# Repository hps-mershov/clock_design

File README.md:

# clock_design
 My first clock design.

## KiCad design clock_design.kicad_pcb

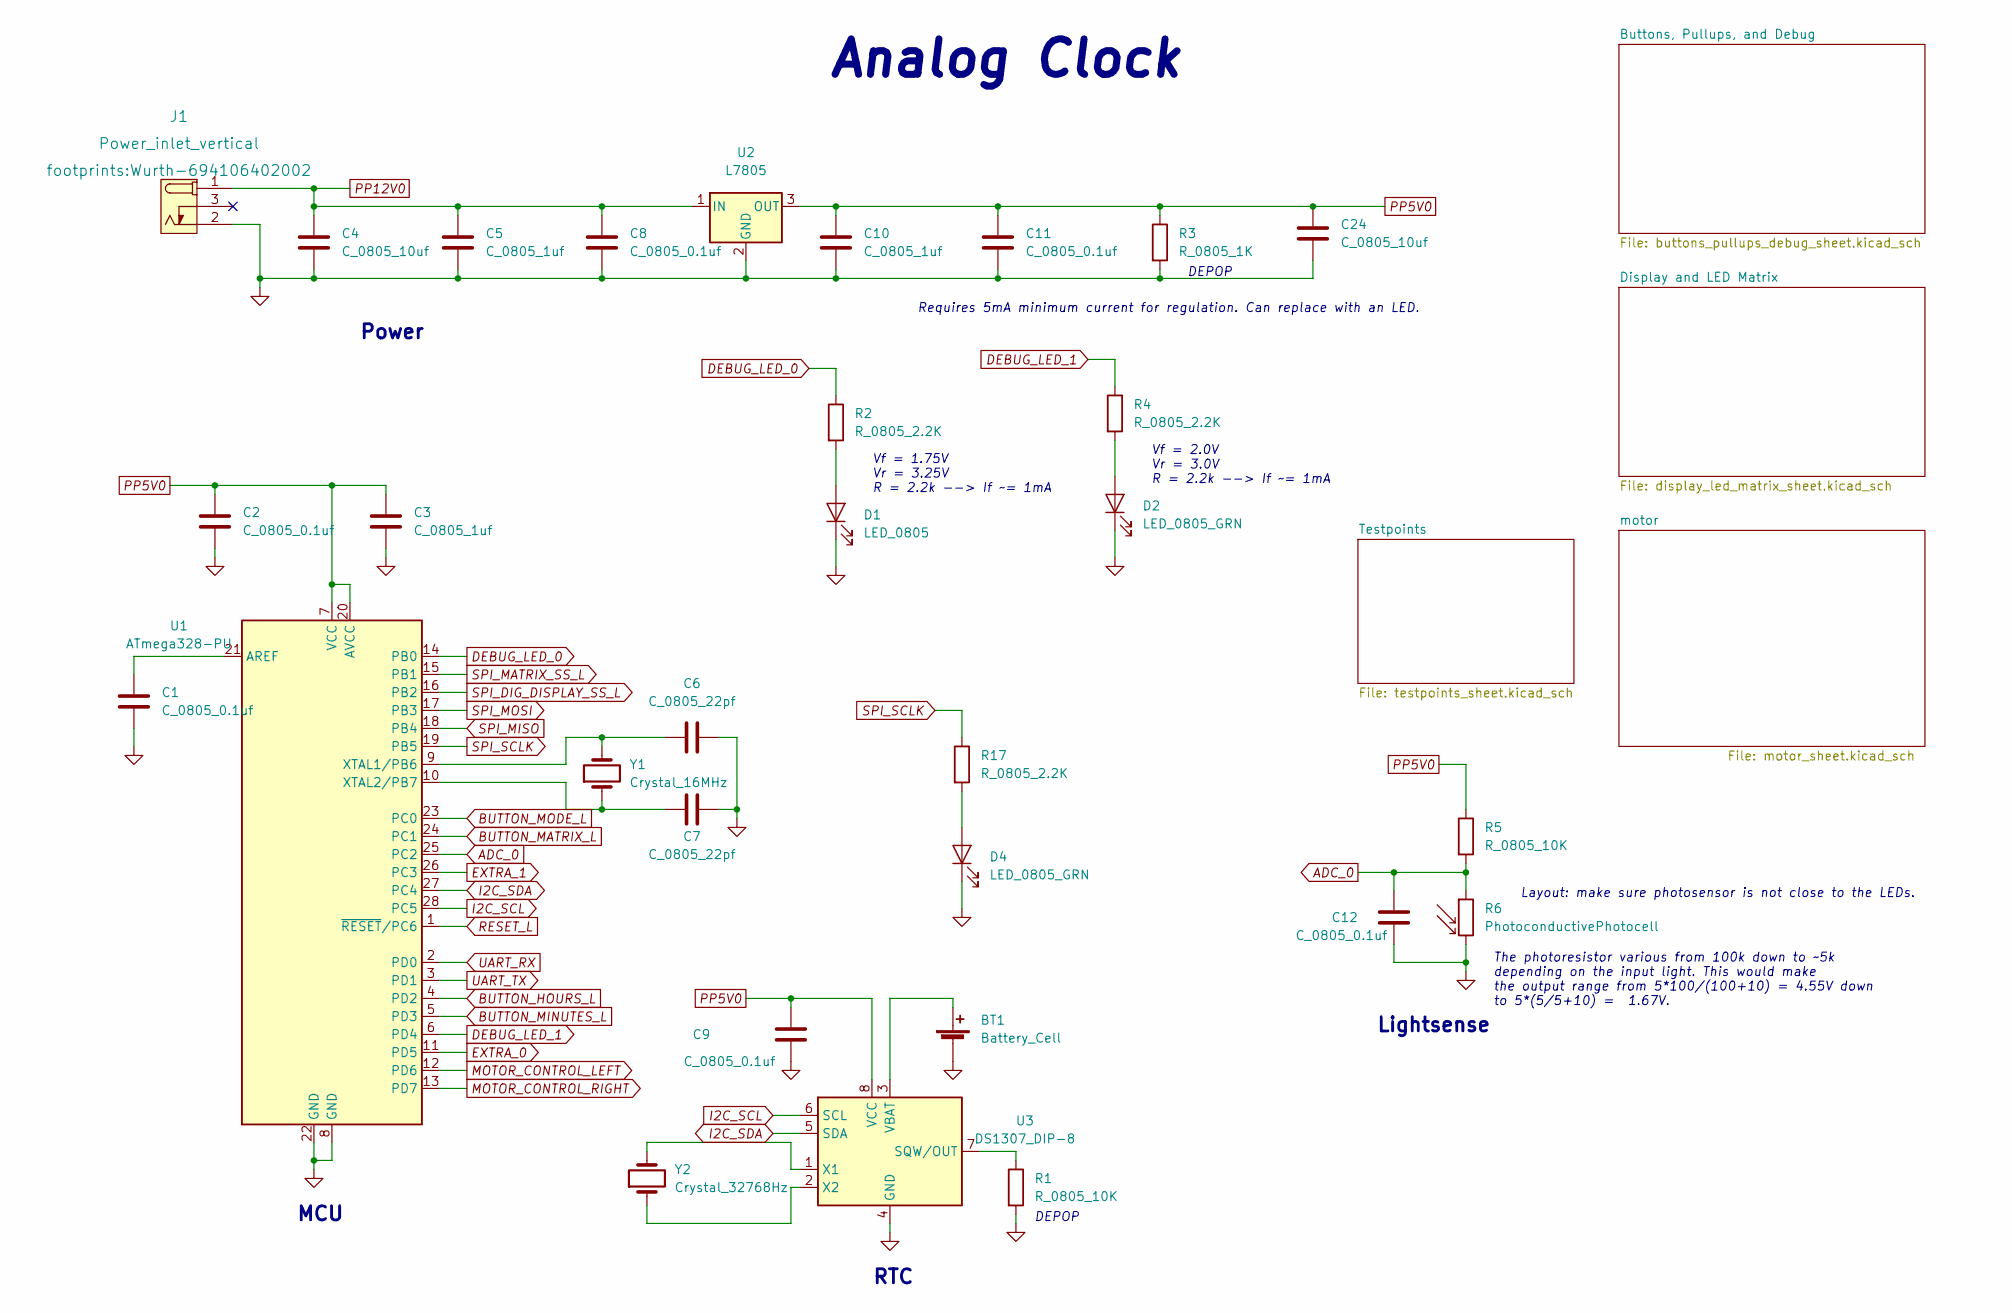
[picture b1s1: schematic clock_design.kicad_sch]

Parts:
BT1: Battery_Cell; BatteryHolder_Keystone_106_1x20mm; MPN BS-7; Digikey PN BS-7-ND
C1, C2, C8, C9, C11, C12: C_0805_0.1uf; C_0805_2012Metric; Voltage N/A; Tolerance N/A; MPN 08055C104KAT2A; Digikey PN 478-1395-1-ND
C3, C5, C10: C_0805_1uf; C_0805_2012Metric; Voltage N/A; Tolerance N/A; MPN CC0805KKX7R8BB105; Digikey PN 311-1456-1-ND
C4, C24: C_0805_10uf; C_0805_2012Metric; Voltage N/A; Tolerance N/A; MPN GRM21BR61E106KA73L; Digikey PN 490-5523-1-ND
C6, C7: C_0805_22pf; C_0805_2012Metric; Voltage N/A; Tolerance N/A; MPN CC0805JRNPO9BN220; Digikey PN 311-1103-1-ND
D1: LED_0805; LED_0805_2012Metric; MPN 150080RS75000; Digikey PN 732-4984-1-ND
D2, D4: LED_0805_GRN; LED_0805_2012Metric; MPN 150080VS75000; Digikey PN 732-4986-1-ND
J1: Power_inlet_vertical; Wurth-694106402002; MPN 694106402002; Digikey PN 732-5931-ND
R1, R5: R_0805_10K; R_0805_2012Metric; Tolerance N/A; MPN RC0805FR-0710KL; Digikey PN 311-10.0KCRCT-ND
R2, R4, R17: R_0805_2.2K; R_0805_2012Metric; Tolerance N/A; MPN N/A; Digikey PN 311-2.20KCRCT-ND
R3: R_0805_1K; R_0805_2012Metric; Tolerance N/A; Mouser PN N/A; Digikey PN RC0805FR-0710KL
R6: PhotoconductivePhotocell; R_LDR_4.9x4.2mm_P2.54mm_Vertical; Voltage N/A; Tolerance N/A; MPN PDV-P8103; Digikey PN PDV-P8103-ND
U1: ATmega328-PU; DIP-28_W7.62mm; MPN ED281DT; Digikey PN ED3050-5-ND
U2: L7805; TO-252-2
U3: DS1307_DIP-8; DIP-8_W7.62mm; MPN A 08-LC-TT; Digikey PN AE9986-ND
Y1: Crystal_16MHz; Crystal_SMD_HC49-SD; MPN ECS-160-20-5PXDN-TR; Digikey PN XC1299CT-ND
Y2: Crystal_32768Hz; Crystal_SMD_2Pin_3.2x1.5mm; MPN Q 0,032768-JTX310-12,5-20-T1-HMR-50K-LF; Digikey PN 1908-1314-1-ND

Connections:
ADC_0: C12.1, R5.2, R6.1, U1.25 (PC2)
BUTTON_HOURS_L: U1.4 (PD2); also elsewhere on the board
BUTTON_MATRIX_L: U1.24 (PC1); also elsewhere on the board
BUTTON_MINUTES_L: U1.5 (PD3); also elsewhere on the board
BUTTON_MODE_L: U1.23 (PC0); also elsewhere on the board
DEBUG_LED_0: R2.1, U1.14 (PB0); also elsewhere on the board
DEBUG_LED_1: R4.1, U1.6 (PD4)
EXTRA_0: U1.11 (PD5); also elsewhere on the board
EXTRA_1: U1.26 (PC3); also elsewhere on the board
GND: BT1.2 (-), C1.2, C2.2, C3.2, C4.2, C5.2, C6.2, C7.2, C8.2, C9.2, C10.2, C11.2, C12.2, C24.2, D1.1 (K), D2.1 (K), D4.1 (K), J1.2 (OUT), R1.2, R3.2, R6.2, U1.8 (GND), U1.22 (GND), U2.2 (GND), U3.4 (GND); also elsewhere on the board
I2C_SCL: U1.28 (PC5), U3.6 (SCL); also elsewhere on the board
I2C_SDA: U1.27 (PC4), U3.5 (SDA); also elsewhere on the board
MOTOR_CONTROL_LEFT: U1.12 (PD6); also elsewhere on the board
MOTOR_CONTROL_RIGHT: U1.13 (PD7); also elsewhere on the board
unnamed: BT1.1 (+), U3.3 (VBAT)
unnamed: C1.1, U1.21 (AREF)
unnamed: C6.1, U1.9 (XTAL1/PB6), Y1.2
unnamed: C7.1, U1.10 (XTAL2/PB7), Y1.1
unnamed: D1.2 (A), R2.2
unnamed: D2.2 (A), R4.2
unnamed: D4.2 (A), R17.2
unnamed: R1.1, U3.7 (SQW/OUT)
unnamed: U3.1 (X1), Y2.2
unnamed: U3.2 (X2), Y2.1
PP5V0: C2.1, C3.1, C9.1, C10.1, C11.1, C24.1, R3.1, R5.1, U1.7 (VCC), U1.20 (AVCC), U2.3 (OUT), U3.8 (VCC); also elsewhere on the board
PP12V0: C4.1, C5.1, C8.1, J1.1 (POLE), U2.1 (IN); also elsewhere on the board
RESET_L: U1.1 (~RESET/PC6); also elsewhere on the board
SPI_DIG_DISPLAY_SS_L: U1.16 (PB2); also elsewhere on the board
SPI_MATRIX_SS_L: U1.15 (PB1); also elsewhere on the board
SPI_MISO: U1.18 (PB4); also elsewhere on the board
SPI_MOSI: U1.17 (PB3); also elsewhere on the board
SPI_SCLK: R17.1, U1.19 (PB5); also elsewhere on the board
UART_RX: U1.2 (PD0); also elsewhere on the board
UART_TX: U1.3 (PD1); also elsewhere on the board

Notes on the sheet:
Vf = 1.75V Vr = 3.25V R = 2.2k --> If ~= 1mA
RTC
MCU
DEPOP
The photoresistor various from 100k down to ~5k depending on the input light. This would make the output range from 5*100/(100+10) = 4.55V down to 5*(5/5+10) = 1.67V.
Analog Clock
Power
Vf = 2.0V Vr = 3.0V R = 2.2k --> If ~= 1mA
Layout: make sure photosensor is not close to the LEDs.
Requires 5mA minimum current for regulation. Can replace with an LED.
Lightsense

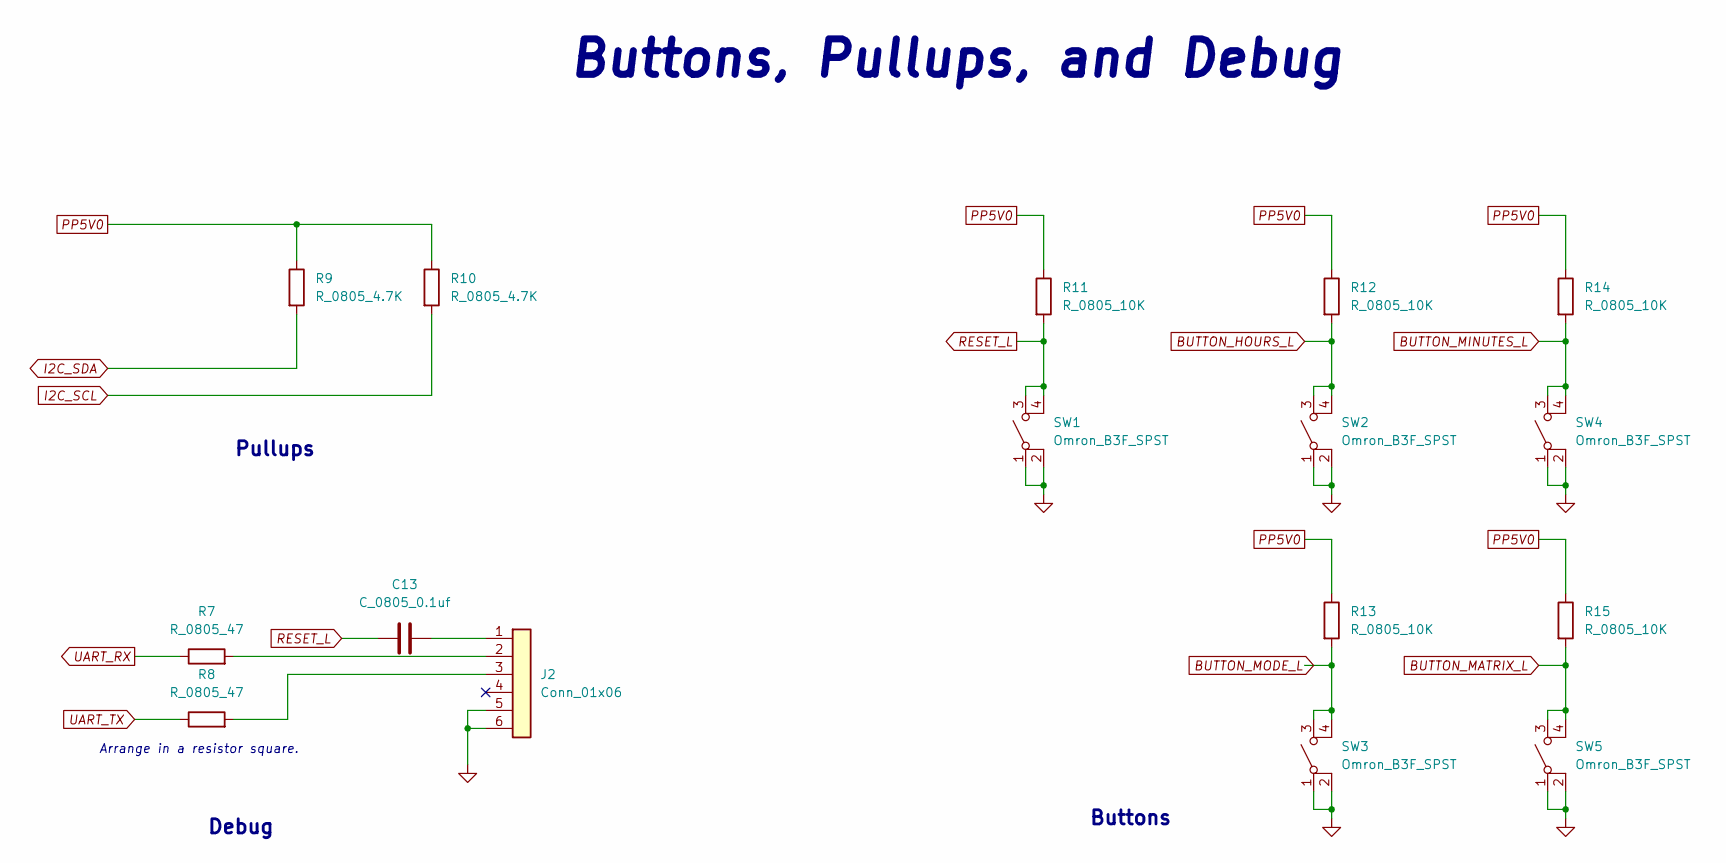
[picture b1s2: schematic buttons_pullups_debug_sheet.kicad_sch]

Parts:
C13: C_0805_0.1uf; C_0805_2012Metric; Voltage N/A; Tolerance N/A; MPN 08055C104KAT2A; Digikey PN 478-1395-1-ND
J2: Conn_01x06; PinHeader_1x06_P2.54mm_Vertical; MPN 61300611121; Digikey PN 732-5319-ND
R7, R8: R_0805_47; R_0805_2012Metric; Tolerance N/A; Mouser PN N/A; Digikey PN RC0805FR-0747RL
R9, R10: R_0805_4.7K; R_0805_2012Metric; Tolerance N/A; MPN RC0805FR-074K7L; Digikey PN 311-4.70KCRCT-ND
R11, R12, R13, R14, R15: R_0805_10K; R_0805_2012Metric; Tolerance N/A; MPN RC0805FR-0710KL; Digikey PN 311-10.0KCRCT-ND
SW1, SW2, SW3, SW4, SW5: Omron_B3F_SPST; SW_SPST_Omron_B3FS-100xP; MPN B3FS-1000P; Digikey PN SW423CT-ND

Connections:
BUTTON_HOURS_L: R12.2, SW2.3 (B), SW2.4 (B); also elsewhere on the board
BUTTON_MATRIX_L: R15.2, SW5.3 (B), SW5.4 (B); also elsewhere on the board
BUTTON_MINUTES_L: R14.2, SW4.3 (B), SW4.4 (B); also elsewhere on the board
BUTTON_MODE_L: R13.2, SW3.3 (B), SW3.4 (B); also elsewhere on the board
GND: J2.5, J2.6, SW1.1 (A), SW1.2 (A), SW2.1 (A), SW2.2 (A), SW3.1 (A), SW3.2 (A), SW4.1 (A), SW4.2 (A), SW5.1 (A), SW5.2 (A); also elsewhere on the board
I2C_SCL: R10.2; also elsewhere on the board
I2C_SDA: R9.2; also elsewhere on the board
unnamed: C13.2, J2.1
unnamed: J2.2, R7.2
unnamed: J2.3, R8.2
PP5V0: R9.1, R10.1, R11.1, R12.1, R13.1, R14.1, R15.1; also elsewhere on the board
RESET_L: C13.1, R11.2, SW1.3 (B), SW1.4 (B); also elsewhere on the board
UART_RX: R7.1; also elsewhere on the board
UART_TX: R8.1; also elsewhere on the board

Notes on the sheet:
Debug
Buttons, Pullups, and Debug
Pullups
Buttons
Arrange in a resistor square.

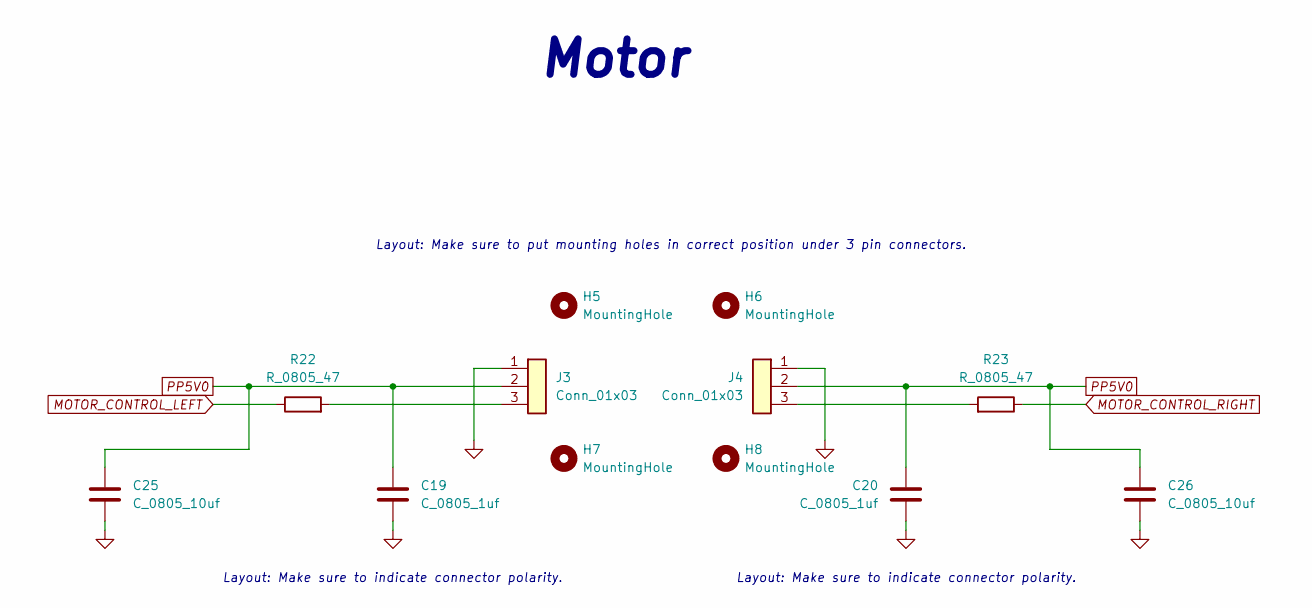
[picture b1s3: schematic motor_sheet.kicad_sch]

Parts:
C19, C20: C_0805_1uf; C_0805_2012Metric; Voltage N/A; Tolerance N/A; MPN CC0805KKX7R8BB105; Digikey PN 311-1456-1-ND
C25, C26: C_0805_10uf; C_0805_2012Metric; Voltage N/A; Tolerance N/A; MPN GRM21BR61E106KA73L; Digikey PN 490-5523-1-ND
H5, H6, H7, H8: MountingHole; MountingHole_3.2mm_M3
J3, J4: Conn_01x03; PinHeader_1x03_P2.54mm_Vertical; MPN 61300311121; Digikey PN 732-5316-ND
R22, R23: R_0805_47; R_0805_2012Metric; Tolerance N/A; Mouser PN N/A; Digikey PN RC0805FR-0747RL

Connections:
GND: C19.2, C20.2, C25.2, C26.2, J3.1, J4.1; also elsewhere on the board
MOTOR_CONTROL_LEFT: R22.1; also elsewhere on the board
MOTOR_CONTROL_RIGHT: R23.1; also elsewhere on the board
unnamed: J3.3, R22.2
unnamed: J4.3, R23.2
PP5V0: C19.1, C20.1, C25.1, C26.1, J3.2, J4.2; also elsewhere on the board

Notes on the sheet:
Motor
Layout: Make sure to indicate connector polarity.
Layout: Make sure to put mounting holes in correct position under 3 pin connectors.

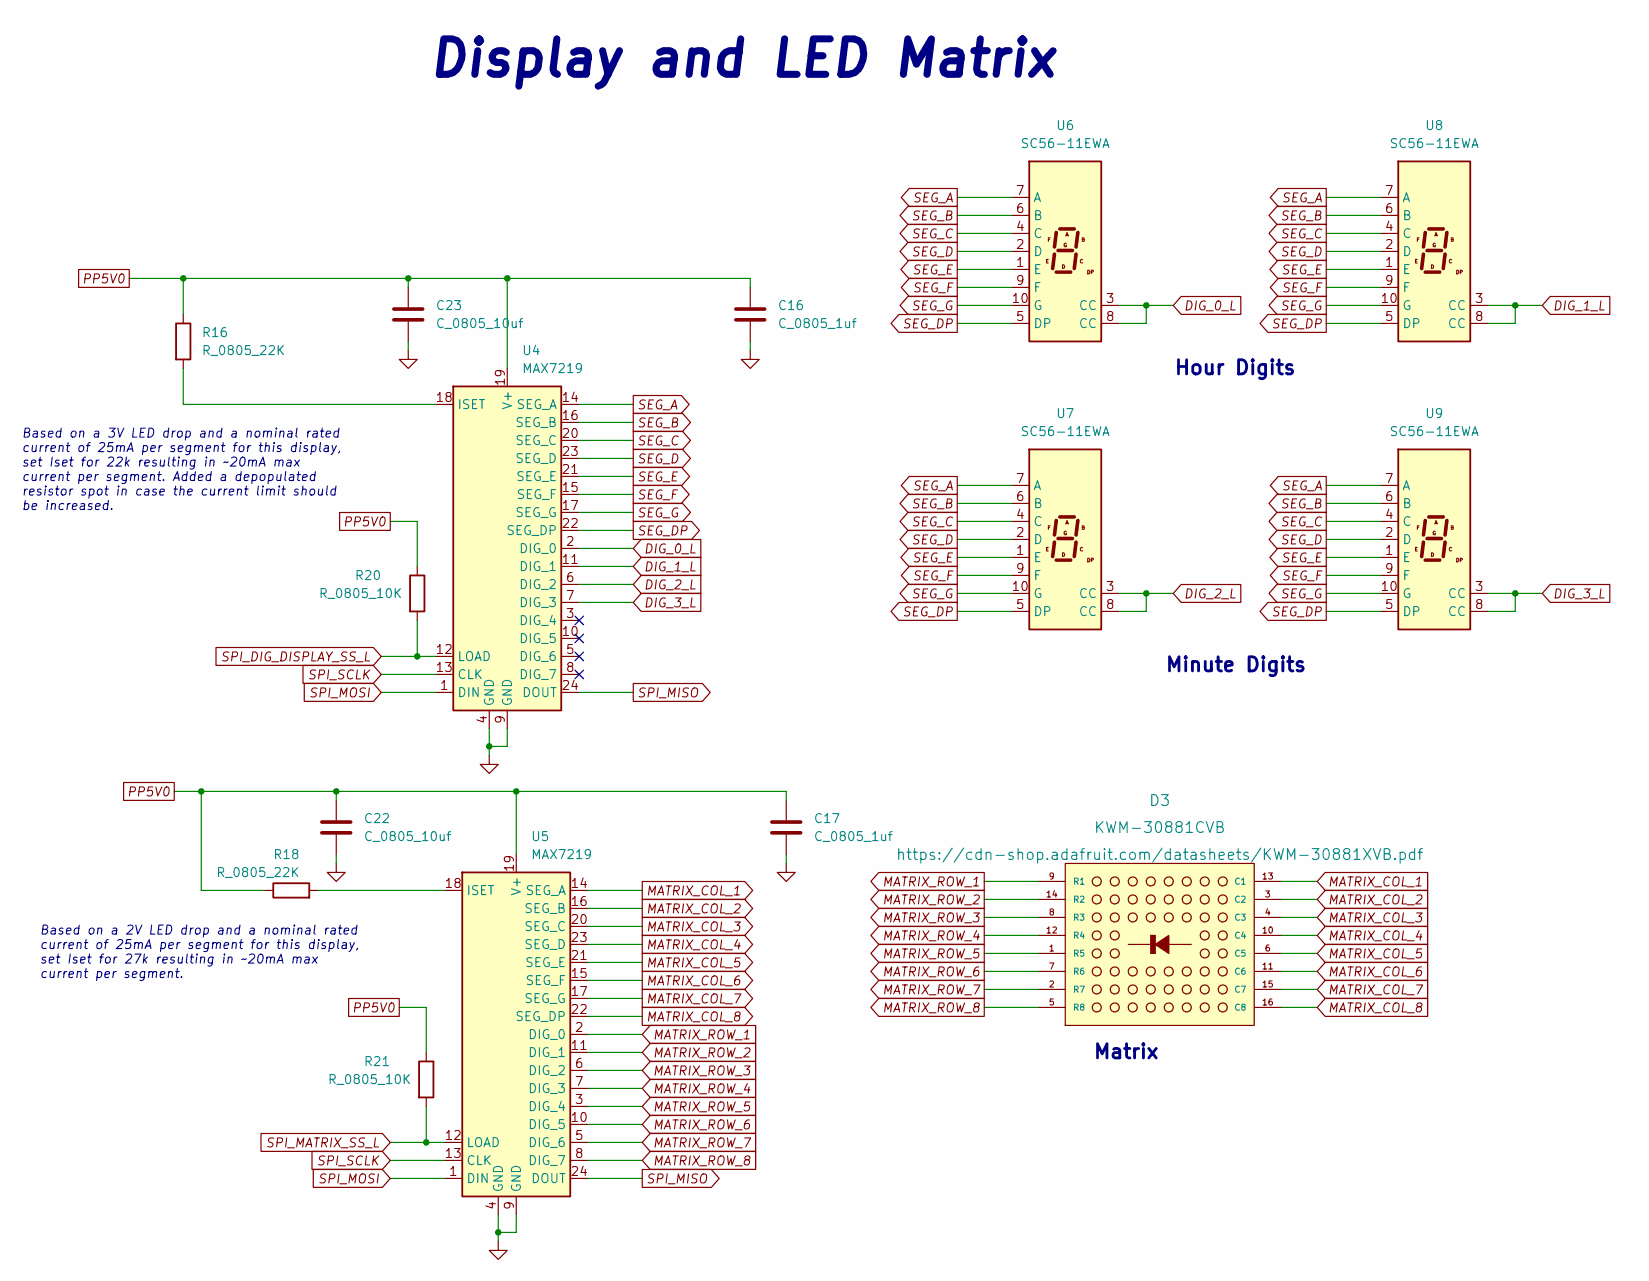
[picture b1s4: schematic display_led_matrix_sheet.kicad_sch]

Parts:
C16, C17: C_0805_1uf; C_0805_2012Metric; Voltage N/A; Tolerance N/A; MPN CC0805KKX7R8BB105; Digikey PN 311-1456-1-ND
C22, C23: C_0805_10uf; C_0805_2012Metric; Voltage N/A; Tolerance N/A; MPN GRM21BR61E106KA73L; Digikey PN 490-5523-1-ND
D3: KWM-30881CVB; MPN KWM-30881CVB; Digikey PN N/A
R16, R18: R_0805_22K; R_0805_2012Metric; Tolerance N/A; MPN RC0805FR-0722KL; Digikey PN 311-22.0KCRCT-ND
R20, R21: R_0805_10K; R_0805_2012Metric; Tolerance N/A; MPN RC0805FR-0710KL; Digikey PN 311-10.0KCRCT-ND
U4, U5: MAX7219; DIP-24_W7.62mm; MPN ED241DT; Digikey PN ED3049-5-ND
U6, U7, U8, U9: SC56-11EWA; Sx56-1xxxxx; Digikey PN 754-1465-5-ND

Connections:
DIG_0_L: U4.2 (DIG_0), U6.3 (CC), U6.8 (CC)
DIG_1_L: U4.11 (DIG_1), U8.3 (CC), U8.8 (CC)
DIG_2_L: U4.6 (DIG_2), U7.3 (CC), U7.8 (CC)
DIG_3_L: U4.7 (DIG_3), U9.3 (CC), U9.8 (CC)
GND: C16.2, C17.2, C22.2, C23.2, U4.4 (GND), U4.9 (GND), U5.4 (GND), U5.9 (GND); also elsewhere on the board
MATRIX_COL_1: D3.13 (C1), U5.14 (SEG_A)
MATRIX_COL_2: D3.3 (C2), U5.16 (SEG_B)
MATRIX_COL_3: D3.4 (C3), U5.20 (SEG_C)
MATRIX_COL_4: D3.10 (C4), U5.23 (SEG_D)
MATRIX_COL_5: D3.6 (C5), U5.21 (SEG_E)
MATRIX_COL_6: D3.11 (C6), U5.15 (SEG_F)
MATRIX_COL_7: D3.15 (C7), U5.17 (SEG_G)
MATRIX_COL_8: D3.16 (C8), U5.22 (SEG_DP)
MATRIX_ROW_1: D3.9 (R1), U5.2 (DIG_0)
MATRIX_ROW_2: D3.14 (R2), U5.11 (DIG_1)
MATRIX_ROW_3: D3.8 (R3), U5.6 (DIG_2)
MATRIX_ROW_4: D3.12 (R4), U5.7 (DIG_3)
MATRIX_ROW_5: D3.1 (R5), U5.3 (DIG_4)
MATRIX_ROW_6: D3.7 (R6), U5.10 (DIG_5)
MATRIX_ROW_7: D3.2 (R7), U5.5 (DIG_6)
MATRIX_ROW_8: D3.5 (R8), U5.8 (DIG_7)
unnamed: R16.2, U4.18 (ISET)
unnamed: R18.2, U5.18 (ISET)
PP5V0: C16.1, C17.1, C22.1, C23.1, R16.1, R18.1, R20.1, R21.1, U4.19 (V+), U5.19 (V+); also elsewhere on the board
SEG_A: U4.14 (SEG_A), U6.7 (A), U7.7 (A), U8.7 (A), U9.7 (A)
SEG_B: U4.16 (SEG_B), U6.6 (B), U7.6 (B), U8.6 (B), U9.6 (B)
SEG_C: U4.20 (SEG_C), U6.4 (C), U7.4 (C), U8.4 (C), U9.4 (C)
SEG_D: U4.23 (SEG_D), U6.2 (D), U7.2 (D), U8.2 (D), U9.2 (D)
SEG_DP: U4.22 (SEG_DP), U6.5 (DP), U7.5 (DP), U8.5 (DP), U9.5 (DP)
SEG_E: U4.21 (SEG_E), U6.1 (E), U7.1 (E), U8.1 (E), U9.1 (E)
SEG_F: U4.15 (SEG_F), U6.9 (F), U7.9 (F), U8.9 (F), U9.9 (F)
SEG_G: U4.17 (SEG_G), U6.10 (G), U7.10 (G), U8.10 (G), U9.10 (G)
SPI_DIG_DISPLAY_SS_L: R20.2, U4.12 (LOAD); also elsewhere on the board
SPI_MATRIX_SS_L: R21.2, U5.12 (LOAD); also elsewhere on the board
SPI_MISO: U4.24 (DOUT), U5.24 (DOUT); also elsewhere on the board
SPI_MOSI: U4.1 (DIN), U5.1 (DIN); also elsewhere on the board
SPI_SCLK: U4.13 (CLK), U5.13 (CLK); also elsewhere on the board

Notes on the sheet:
Hour Digits
Minute Digits
Based on a 3V LED drop and a nominal rated current of 25mA per segment for this display, set Iset for 22k resulting in ~20mA max current per segment. Added a depopulated resistor spot in case the current limit should be increased.
Matrix
Display and LED Matrix
Based on a 2V LED drop and a nominal rated current of 25mA per segment for this display, set Iset for 27k resulting in ~20mA max current per segment.

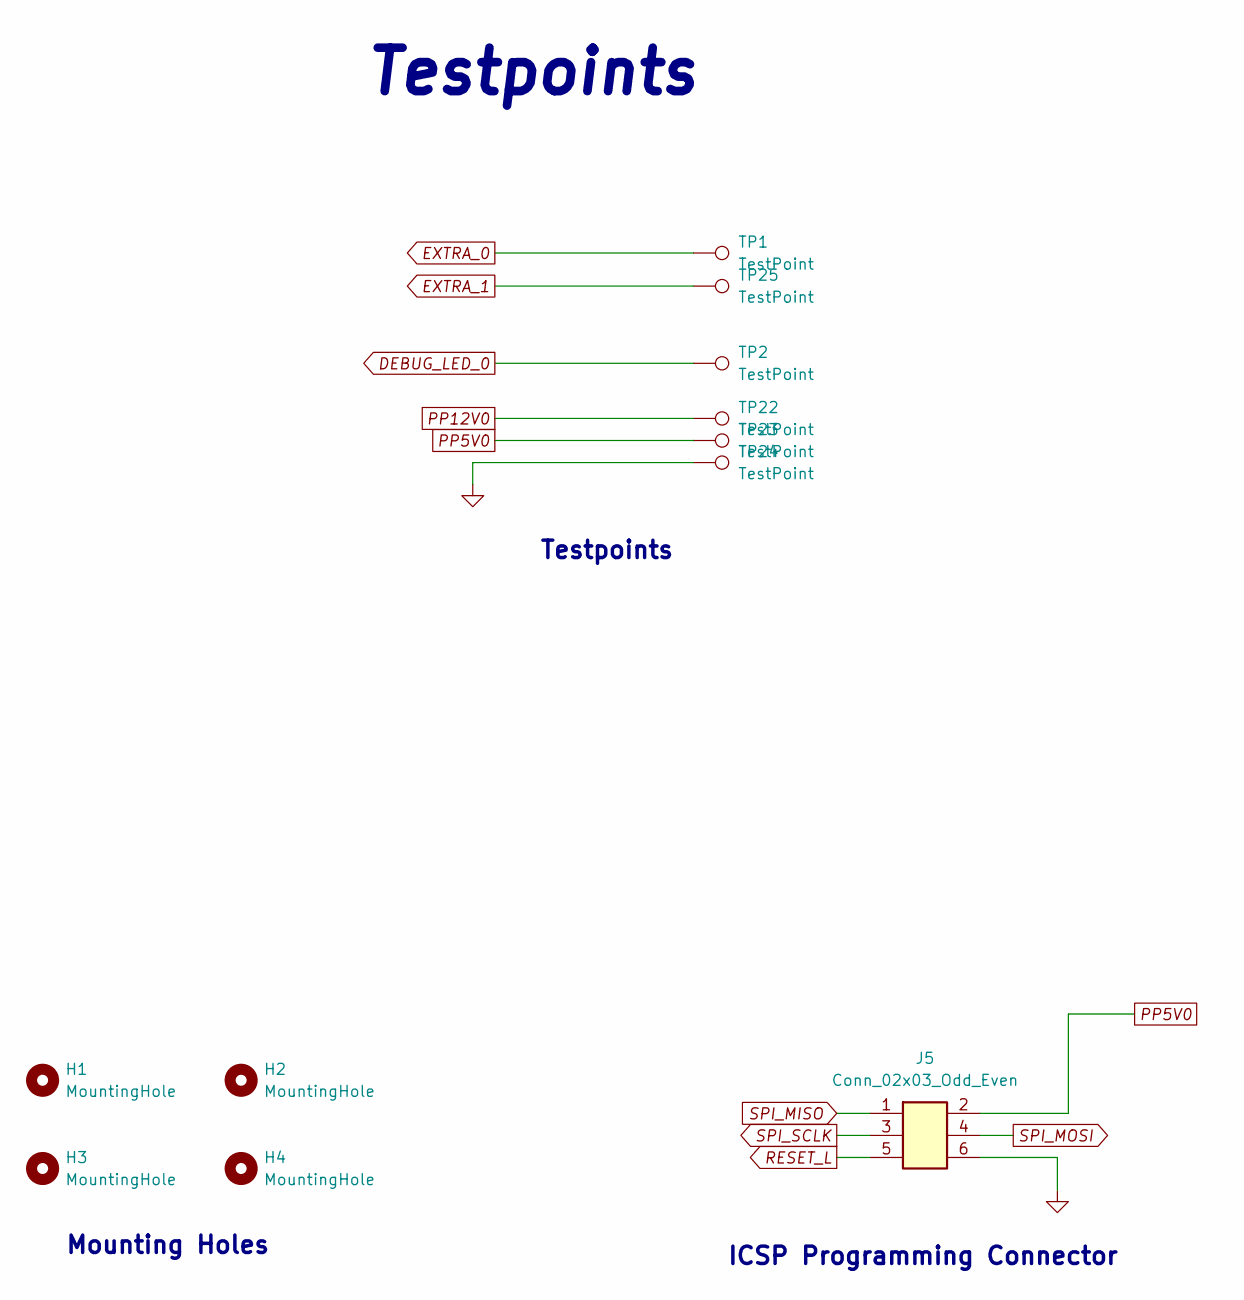
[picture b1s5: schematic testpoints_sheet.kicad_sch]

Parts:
H1, H2, H3, H4: MountingHole; MountingHole_3.2mm_M3
J5: Conn_02x03_Odd_Even; PinHeader_2x03_P2.54mm_Vertical; MPN PRPC003DAAN-RC; Digikey PN S2011EC-03-ND
TP1, TP2, TP22, TP23, TP24, TP25: TestPoint; TestPoint_THTPad_D2.0mm_Drill1.0mm

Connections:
DEBUG_LED_0: TP2.1; also elsewhere on the board
EXTRA_0: TP1.1; also elsewhere on the board
EXTRA_1: TP25.1; also elsewhere on the board
GND: J5.6, TP24.1; also elsewhere on the board
PP5V0: J5.2, TP23.1; also elsewhere on the board
PP12V0: TP22.1; also elsewhere on the board
RESET_L: J5.5; also elsewhere on the board
SPI_MISO: J5.1; also elsewhere on the board
SPI_MOSI: J5.4; also elsewhere on the board
SPI_SCLK: J5.3; also elsewhere on the board

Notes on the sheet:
Mounting Holes
ICSP Programming Connector
Testpoints

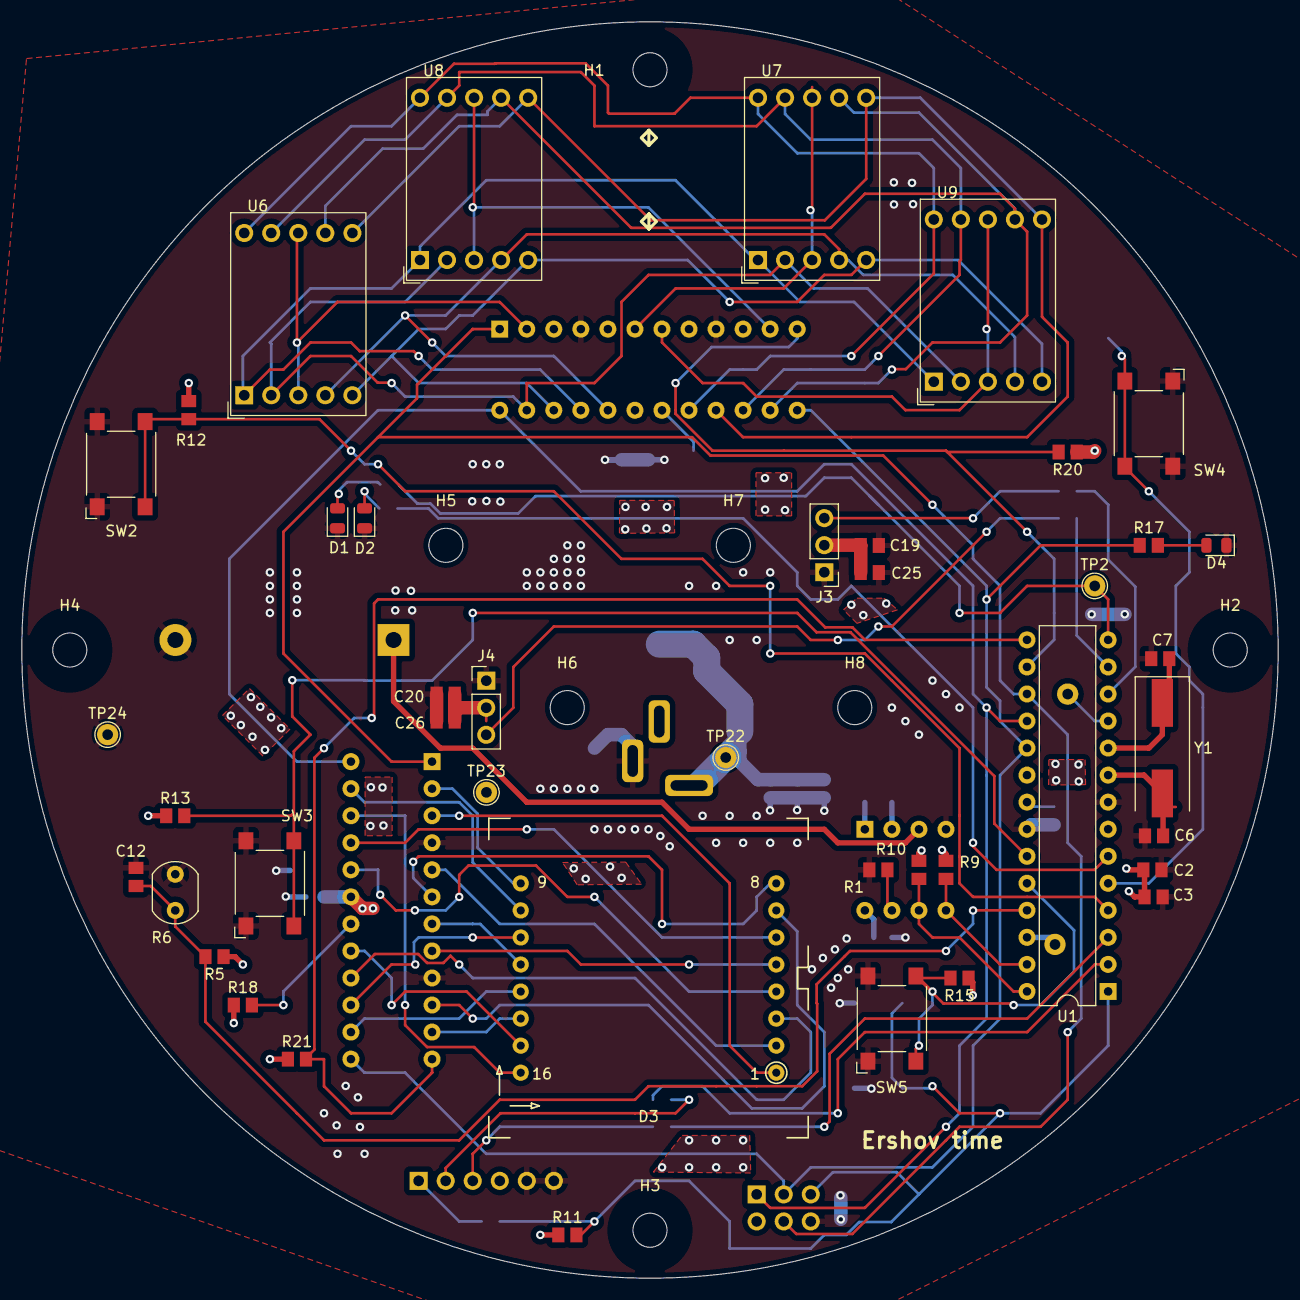
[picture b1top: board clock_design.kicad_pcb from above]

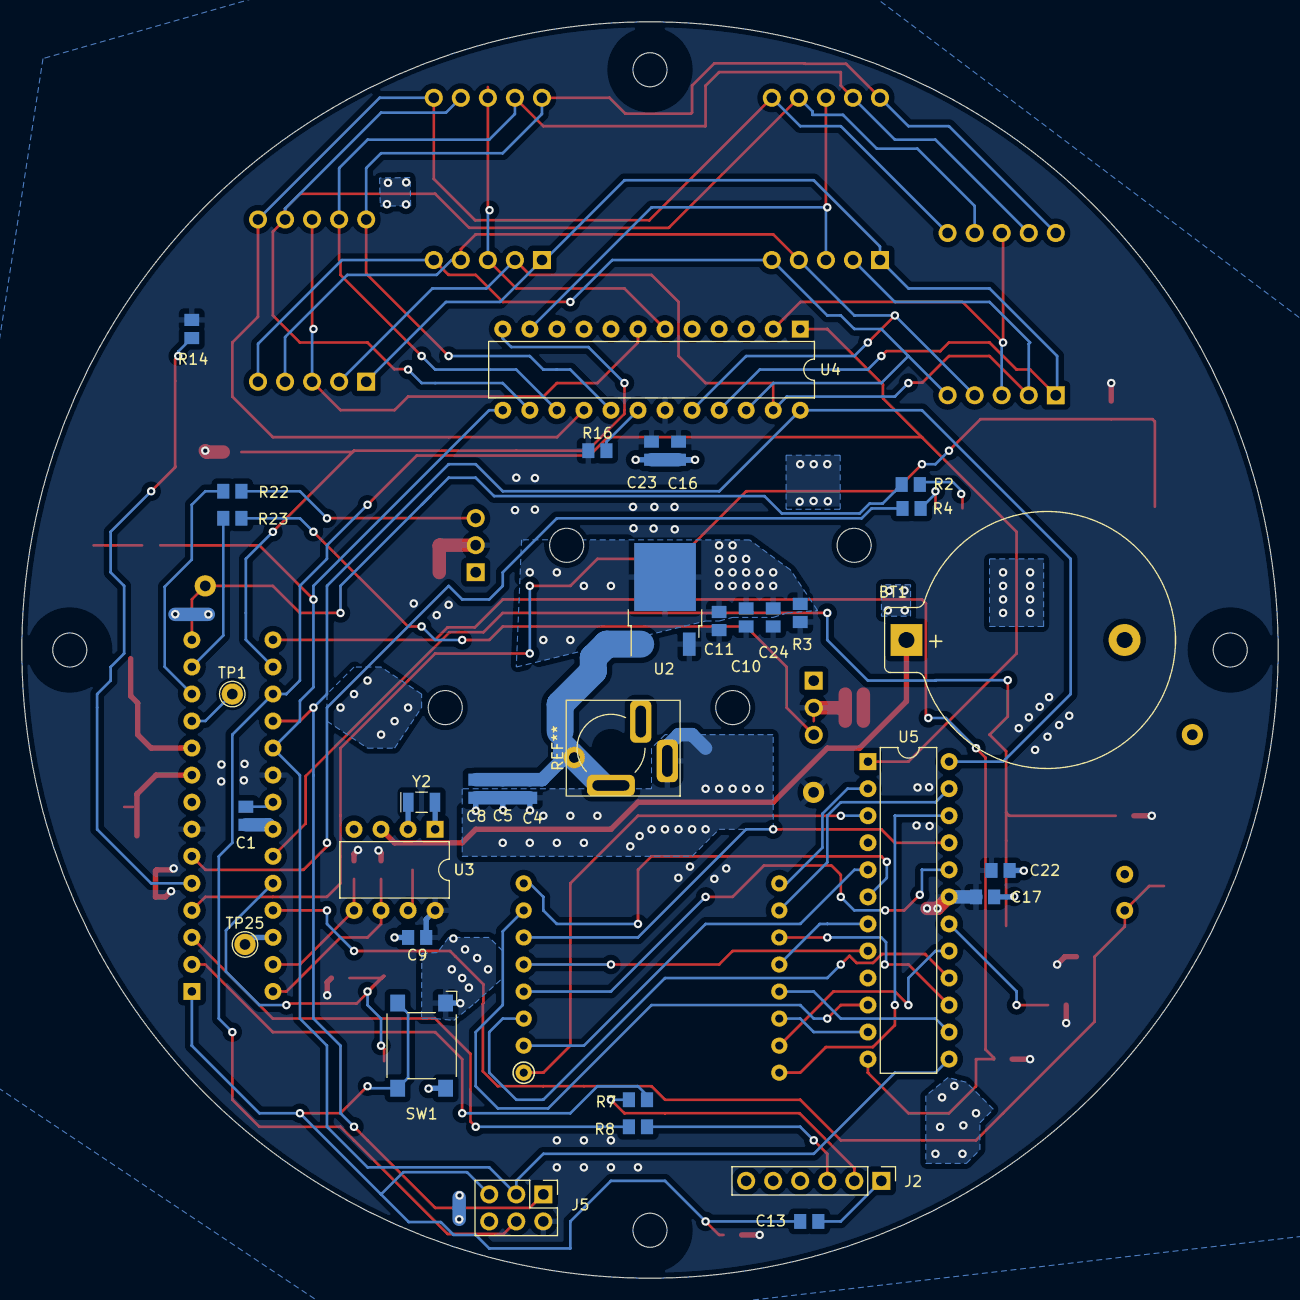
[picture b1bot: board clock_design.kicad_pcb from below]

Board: 2 copper layers, 118.0 x 118.0 mm, 84 parts (34 on the bottom side), 69 nets.

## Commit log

2022-07-15 Added new BOM (a single LED + resistor).
2022-07-15 Routing in progress...
2022-07-19 Initial gerber out
    Got all of the files for gereber out
2022-07-19 gerber zip added for DFM
2022-07-21 final gerber (no chang)
